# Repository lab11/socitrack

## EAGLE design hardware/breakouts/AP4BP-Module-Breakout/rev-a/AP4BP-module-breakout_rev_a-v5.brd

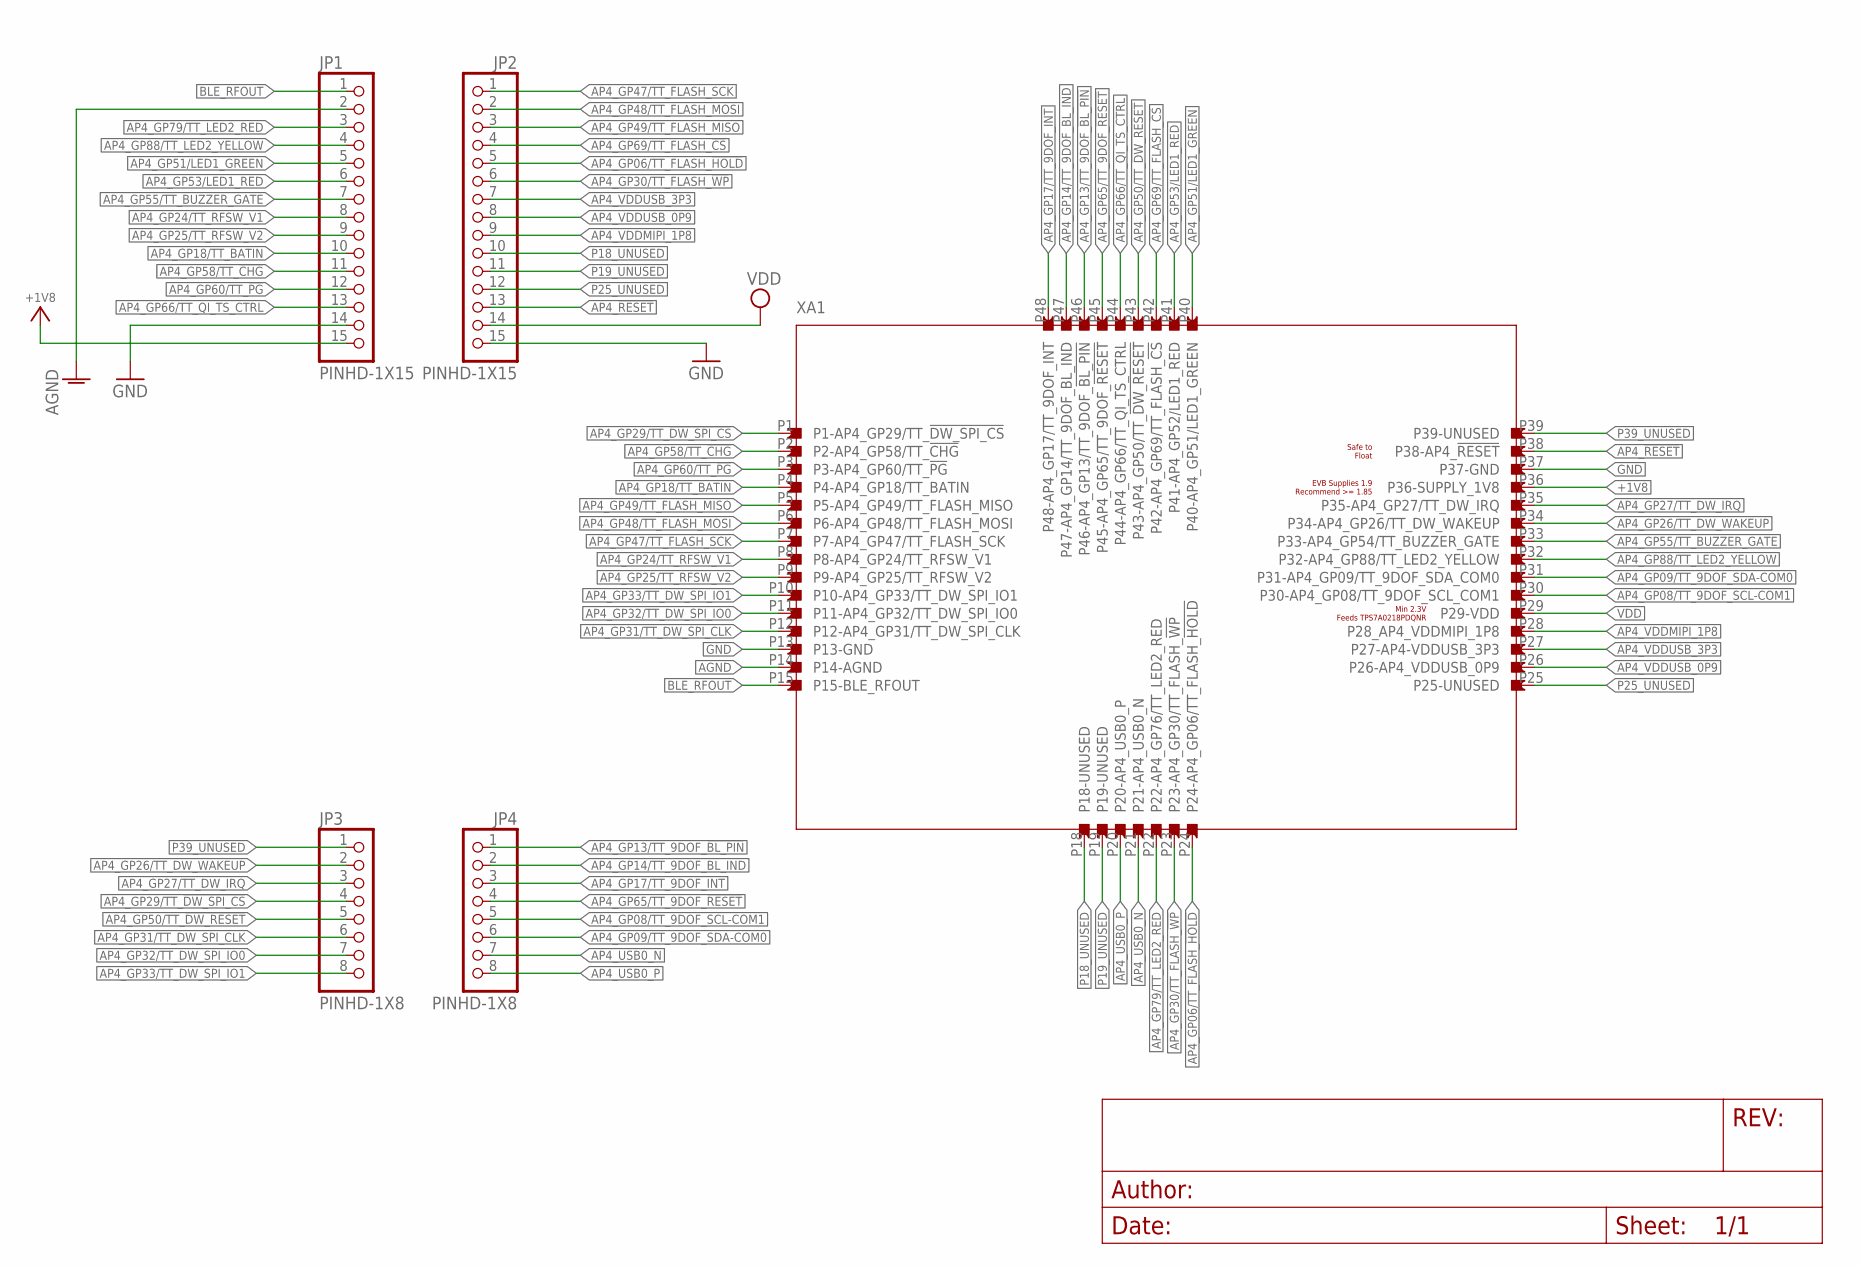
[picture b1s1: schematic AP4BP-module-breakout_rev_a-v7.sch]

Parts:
JP1, JP2: PINHD-1X15; 1X15
JP3, JP4: PINHD-1X8; 1X08
XA1: APOLLO4_BLUEPLUS_MODULE

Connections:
+1V8: JP1.15, XA1.P36 (P36-SUPPLY_1V8)
AGND: JP1.2, XA1.P14 (P14-AGND)
AP4_!RESET: JP2.13, XA1.P38 (P38-AP4_!RESET)
AP4_GP06/TT_FLASH_!HOLD: JP2.5, XA1.P24 (P24-AP4_GP06/TT_FLASH_!HOLD)
AP4_GP08/TT_9DOF_SCL-COM1: JP4.5, XA1.P30 (P30-AP4_GP08/TT_9DOF_SCL_COM1)
AP4_GP09/TT_9DOF_SDA-COM0: JP4.6, XA1.P31 (P31-AP4_GP09/TT_9DOF_SDA_COM0)
AP4_GP13/TT_9DOF_!BL_PIN: JP4.1, XA1.P46 (P46-AP4_GP13/TT_9DOF_!BL_PIN)
AP4_GP14/TT_9DOF_BL_IND: JP4.2, XA1.P47 (P47-AP4_GP14/TT_9DOF_BL_IND)
AP4_GP17/TT_9DOF_INT: JP4.3, XA1.P48 (P48-AP4_GP17/TT_9DOF_INT)
AP4_GP18/TT_BATIN: JP1.10, XA1.P4 (P4-AP4_GP18/TT_BATIN)
AP4_GP24/TT_RFSW_V1: JP1.8, XA1.P8 (P8-AP4_GP24/TT_RFSW_V1)
AP4_GP25/TT_RFSW_V2: JP1.9, XA1.P9 (P9-AP4_GP25/TT_RFSW_V2)
AP4_GP26/TT_DW_WAKEUP: JP3.2, XA1.P34 (P34-AP4_GP26/TT_DW_WAKEUP)
AP4_GP27/TT_DW_IRQ: JP3.3, XA1.P35 (P35-AP4_GP27/TT_DW_IRQ)
AP4_GP29/TT_!DW_SPI_CS: JP3.4, XA1.P1 (P1-AP4_GP29/TT_!DW_SPI_CS)
AP4_GP30/TT_FLASH_!WP: JP2.6, XA1.P23 (P23-AP4_GP30/TT_FLASH_!WP)
AP4_GP31/TT_DW_SPI_CLK: JP3.6, XA1.P12 (P12-AP4_GP31/TT_DW_SPI_CLK)
AP4_GP32/TT_DW_SPI_IO0: JP3.7, XA1.P11 (P11-AP4_GP32/TT_DW_SPI_IO0)
AP4_GP33/TT_DW_SPI_IO1: JP3.8, XA1.P10 (P10-AP4_GP33/TT_DW_SPI_IO1)
AP4_GP47/TT_FLASH_SCK: JP2.1, XA1.P7 (P7-AP4_GP47/TT_FLASH_SCK)
AP4_GP48/TT_FLASH_MOSI: JP2.2, XA1.P6 (P6-AP4_GP48/TT_FLASH_MOSI)
AP4_GP49/TT_FLASH_MISO: JP2.3, XA1.P5 (P5-AP4_GP49/TT_FLASH_MISO)
AP4_GP50/TT_!DW_RESET: JP3.5, XA1.P43 (P43-AP4_GP50/TT_!DW_RESET)
AP4_GP51/LED1_GREEN: JP1.5, XA1.P40 (P40-AP4_GP51/LED1_GREEN)
AP4_GP53/LED1_RED: JP1.6, XA1.P41 (P41-AP4_GP52/LED1_RED)
AP4_GP55/TT_BUZZER_GATE: JP1.7, XA1.P33 (P33-AP4_GP54/TT_BUZZER_GATE)
AP4_GP58/TT_!CHG: JP1.11, XA1.P2 (P2-AP4_GP58/TT_!CHG)
AP4_GP60/TT_!PG: JP1.12, XA1.P3 (P3-AP4_GP60/TT_!PG)
AP4_GP65/TT_9DOF_!RESET: JP4.4, XA1.P45 (P45-AP4_GP65/TT_9DOF_!RESET)
AP4_GP66/TT_QI_TS_CTRL: JP1.13, XA1.P44 (P44-AP4_GP66/TT_QI_TS_CTRL)
AP4_GP69/TT_FLASH_!CS: JP2.4, XA1.P42 (P42-AP4_GP69/TT_FLASH_!CS)
AP4_GP79/TT_LED2_RED: JP1.3, XA1.P22 (P22-AP4_GP76/TT_LED2_RED)
AP4_GP88/TT_LED2_YELLOW: JP1.4, XA1.P32 (P32-AP4_GP88/TT_LED2_YELLOW)
AP4_USB0_N: JP4.7, XA1.P21 (P21-AP4_USB0_N)
AP4_USB0_P: JP4.8, XA1.P20 (P20-AP4_USB0_P)
AP4_VDDMIPI_1P8: JP2.9, XA1.P28 (P28_AP4_VDDMIPI_1P8)
AP4_VDDUSB_0P9: JP2.8, XA1.P26 (P26-AP4_VDDUSB_0P9)
AP4_VDDUSB_3P3: JP2.7, XA1.P27 (P27-AP4-VDDUSB_3P3)
BLE_RFOUT: JP1.1, XA1.P15 (P15-BLE_RFOUT)
GND: JP1.14, JP2.15, XA1.P13 (P13-GND), XA1.P37 (P37-GND)
P18_UNUSED: JP2.10, XA1.P18 (P18-UNUSED)
P19_UNUSED: JP2.11, XA1.P19 (P19-UNUSED)
P25_UNUSED: JP2.12, XA1.P25 (P25-UNUSED)
P39_UNUSED: JP3.1, XA1.P39 (P39-UNUSED)
VDD: JP2.14, XA1.P29 (P29-VDD)

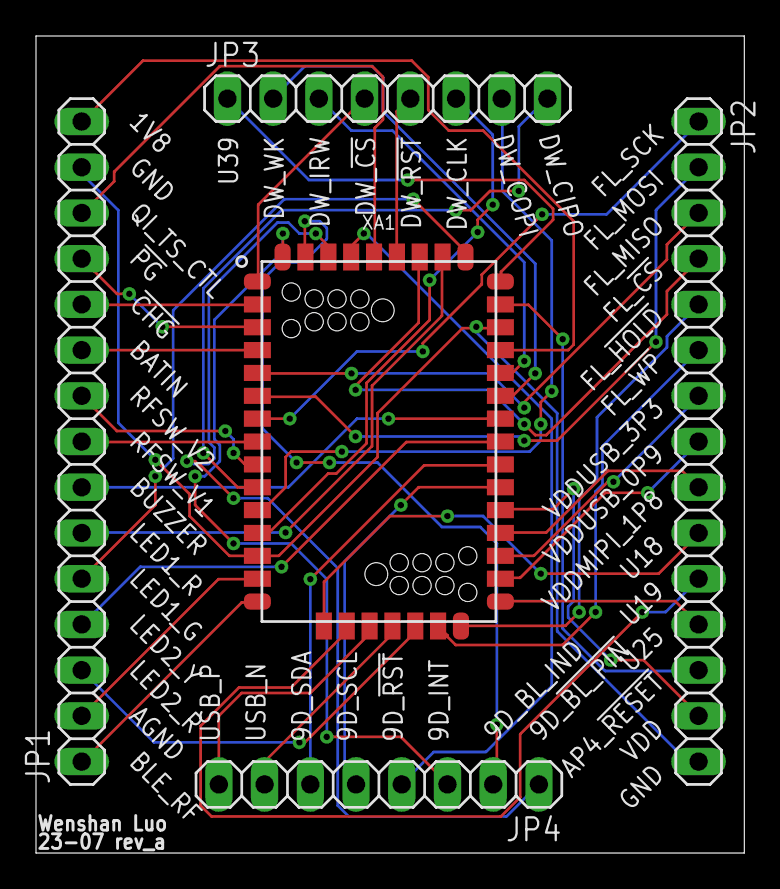
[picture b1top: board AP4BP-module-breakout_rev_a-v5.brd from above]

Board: 2 copper layers, 39.4 x 45.4 mm, 5 parts (0 on the bottom side), 45 nets.

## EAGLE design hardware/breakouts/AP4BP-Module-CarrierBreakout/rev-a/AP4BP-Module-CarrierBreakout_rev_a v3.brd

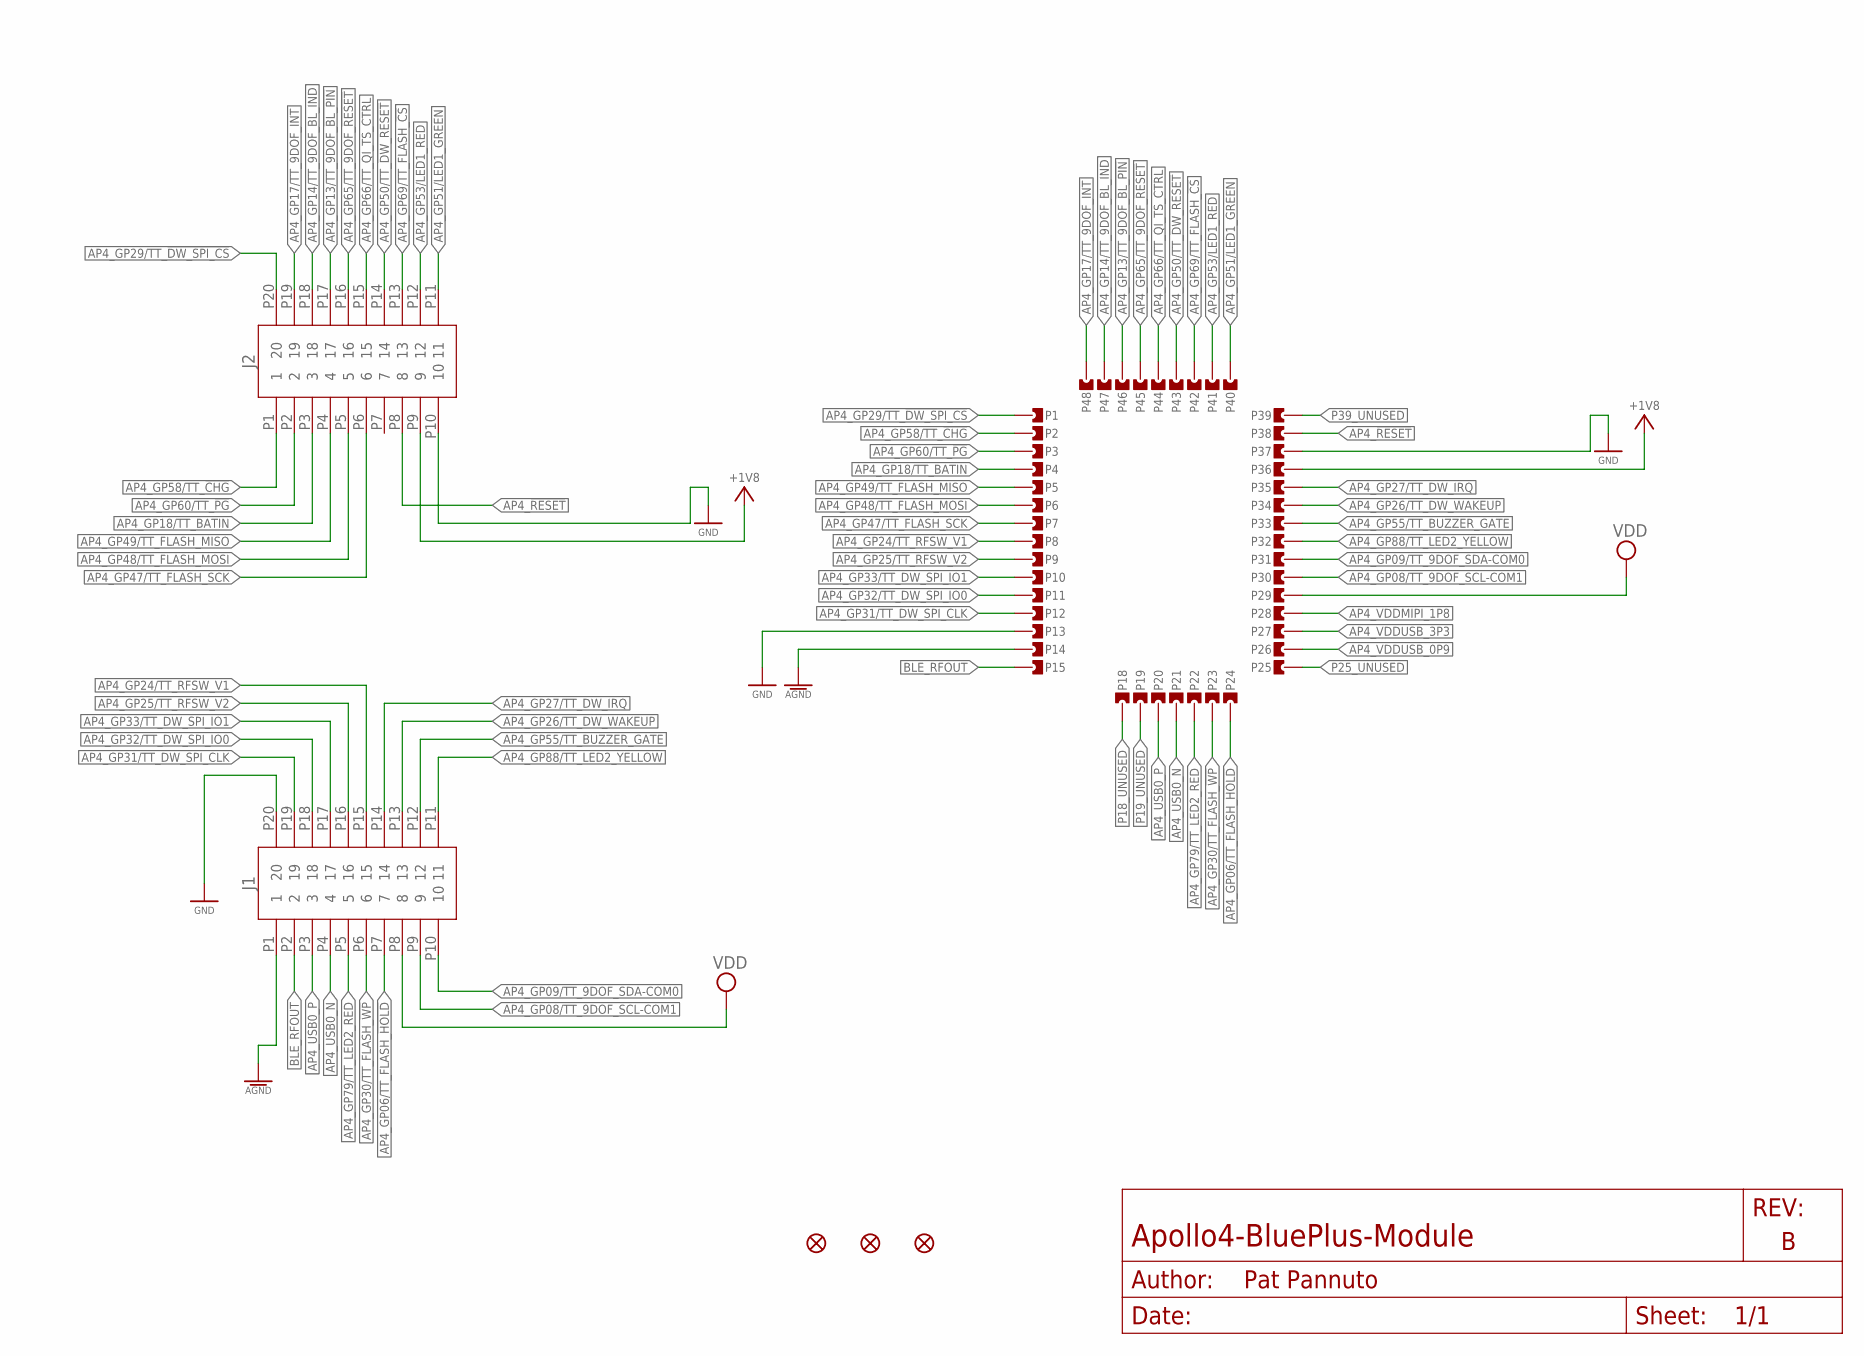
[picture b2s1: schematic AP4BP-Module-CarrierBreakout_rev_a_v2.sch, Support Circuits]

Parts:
FD1, FD2, FD3: FIDUCIALUFIDUCIAL; FIDUCIAL-MICRO
J1, J2: PINHEAD-SMD-1MM-2X10
P1, P2, P3, P4, P5, P6, P7, P8, P9, P10, P11, P12, P13, P14, P15, P18, P19, P20, P21, P22, P23, P24, P25, P26, P27, P28, P29, P30, P31, P32, P33, P34, P35, P36, P37, P38, P39, P40, P41, P42, P43, P44, P45, P46, P47, P48: CASTELLATION4L; CASTELLATION-0.55MM_DRILL-4L

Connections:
+1V8: J2.P9 (9), P36.P$1, P36.P$2, P36.P$3
AGND: J1.P1 (1), P14.P$1, P14.P$2, P14.P$3
AP4_!RESET: J2.P8 (8), P38.P$1, P38.P$2, P38.P$3
AP4_GP06/TT_FLASH_!HOLD: J1.P7 (7), P24.P$1, P24.P$2, P24.P$3
AP4_GP08/TT_9DOF_SCL-COM1: J1.P9 (9), P30.P$1, P30.P$2, P30.P$3
AP4_GP09/TT_9DOF_SDA-COM0: J1.P10 (10), P31.P$1, P31.P$2, P31.P$3
AP4_GP13/TT_9DOF_!BL_PIN: J2.P17 (17), P46.P$1, P46.P$2, P46.P$3
AP4_GP14/TT_9DOF_BL_IND: J2.P18 (18), P47.P$1, P47.P$2, P47.P$3
AP4_GP17/TT_9DOF_INT: J2.P19 (19), P48.P$1, P48.P$2, P48.P$3
AP4_GP18/TT_BATIN: J2.P3 (3), P4.P$1, P4.P$2, P4.P$3
AP4_GP24/TT_RFSW_V1: J1.P15 (15), P8.P$1, P8.P$2, P8.P$3
AP4_GP25/TT_RFSW_V2: J1.P16 (16), P9.P$1, P9.P$2, P9.P$3
AP4_GP26/TT_DW_WAKEUP: J1.P13 (13), P34.P$1, P34.P$2, P34.P$3
AP4_GP27/TT_DW_IRQ: J1.P14 (14), P35.P$1, P35.P$2, P35.P$3
AP4_GP29/TT_!DW_SPI_CS: J2.P20 (20), P1.P$1, P1.P$2, P1.P$3
AP4_GP30/TT_FLASH_!WP: J1.P6 (6), P23.P$1, P23.P$2, P23.P$3
AP4_GP31/TT_DW_SPI_CLK: J1.P19 (19), P12.P$1, P12.P$2, P12.P$3
AP4_GP32/TT_DW_SPI_IO0: J1.P18 (18), P11.P$1, P11.P$2, P11.P$3
AP4_GP33/TT_DW_SPI_IO1: J1.P17 (17), P10.P$1, P10.P$2, P10.P$3
AP4_GP47/TT_FLASH_SCK: J2.P6 (6), P7.P$1, P7.P$2, P7.P$3
AP4_GP48/TT_FLASH_MOSI: J2.P5 (5), P6.P$1, P6.P$2, P6.P$3
AP4_GP49/TT_FLASH_MISO: J2.P4 (4), P5.P$1, P5.P$2, P5.P$3
AP4_GP50/TT_!DW_RESET: J2.P14 (14), P43.P$1, P43.P$2, P43.P$3
AP4_GP51/LED1_GREEN: J2.P11 (11), P40.P$1, P40.P$2, P40.P$3
AP4_GP53/LED1_RED: J2.P12 (12), P41.P$1, P41.P$2, P41.P$3
AP4_GP55/TT_BUZZER_GATE: J1.P12 (12), P33.P$1, P33.P$2, P33.P$3
AP4_GP58/TT_!CHG: J2.P1 (1), P2.P$1, P2.P$2, P2.P$3
AP4_GP60/TT_!PG: J2.P2 (2), P3.P$1, P3.P$2, P3.P$3
AP4_GP65/TT_9DOF_!RESET: J2.P16 (16), P45.P$1, P45.P$2, P45.P$3
AP4_GP66/TT_QI_TS_CTRL: J2.P15 (15), P44.P$1, P44.P$2, P44.P$3
AP4_GP69/TT_FLASH_!CS: J2.P13 (13), P42.P$1, P42.P$2, P42.P$3
AP4_GP79/TT_LED2_RED: J1.P5 (5), P22.P$1, P22.P$2, P22.P$3
AP4_GP88/TT_LED2_YELLOW: J1.P11 (11), P32.P$1, P32.P$2, P32.P$3
AP4_USB0_N: J1.P4 (4), P21.P$1, P21.P$2, P21.P$3
AP4_USB0_P: J1.P3 (3), P20.P$1, P20.P$2, P20.P$3
AP4_VDDMIPI_1P8: P28.P$1, P28.P$2, P28.P$3
AP4_VDDUSB_0P9: P26.P$1, P26.P$2, P26.P$3
AP4_VDDUSB_3P3: P27.P$1, P27.P$2, P27.P$3
BLE_RFOUT: J1.P2 (2), P15.P$1, P15.P$2, P15.P$3
GND: J1.P20 (20), J2.P10 (10), P13.P$1, P13.P$2, P13.P$3, P37.P$1, P37.P$2, P37.P$3
P18_UNUSED: P18.P$1, P18.P$2, P18.P$3
P19_UNUSED: P19.P$1, P19.P$2, P19.P$3
P25_UNUSED: P25.P$1, P25.P$2, P25.P$3
P39_UNUSED: P39.P$1, P39.P$2, P39.P$3
VDD: J1.P8 (8), P29.P$1, P29.P$2, P29.P$3

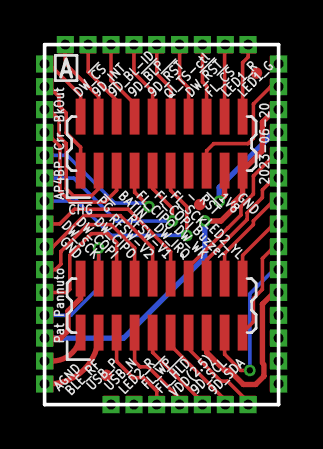
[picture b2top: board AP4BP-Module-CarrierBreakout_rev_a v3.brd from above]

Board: 2 copper layers, 13.0 x 20.0 mm, 51 parts (0 on the bottom side), 45 nets.

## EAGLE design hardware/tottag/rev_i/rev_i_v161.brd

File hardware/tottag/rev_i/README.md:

Rev i
=====

This is now stored in the Fusion Cloud (sigh), with their "version control"
(double sigh).

This is a one-off export of the state of the project when shipped to
manufacture, as well as the design files from CircuitHub (CM making boards).

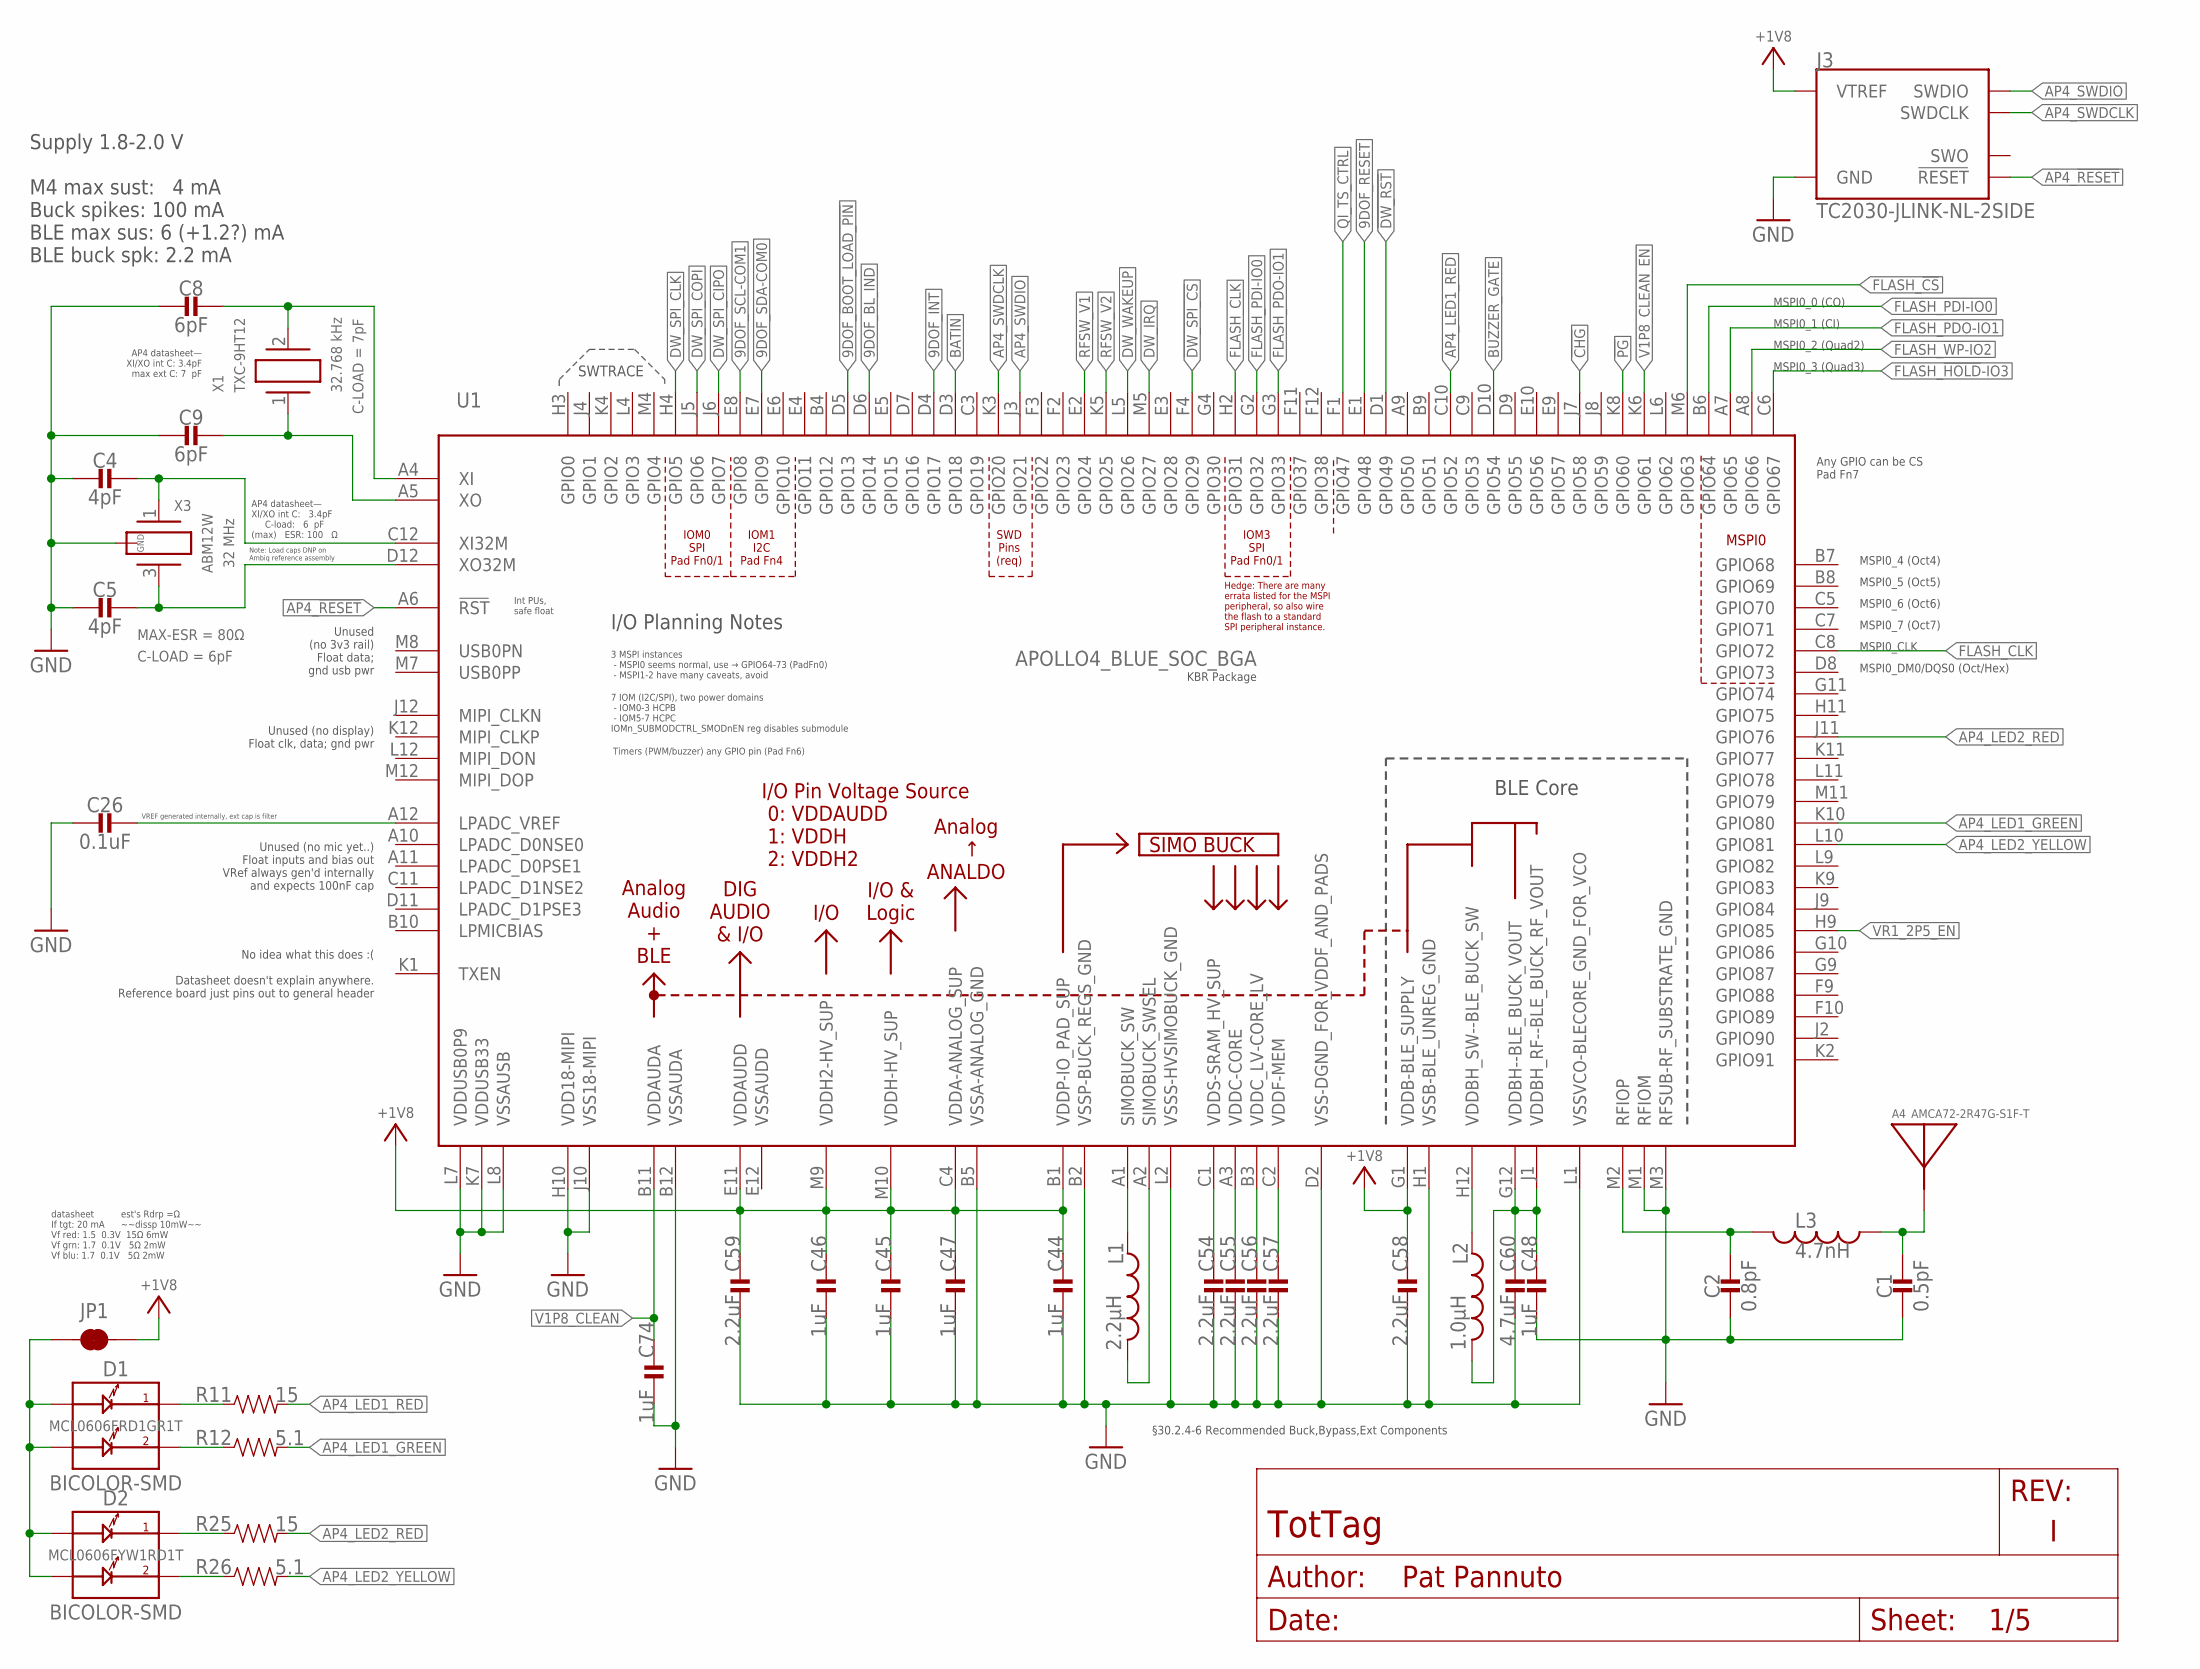
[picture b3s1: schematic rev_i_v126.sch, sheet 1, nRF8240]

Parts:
A4: AMCA72-2R47G-S1F-T; AMCA72-2R470G-S1F-T
C1: 0.5pF; 0402_CAP; MPN GJM1555C1HR50WB01D
C2: 0.8pF; 0402_CAP; MPN GJM1555C1HR80WB01D
C4, C5: 4pF; 0201_CAP; MPN GRM0335C1H4R0BA01D
C8, C9: 6pF; 0201_CAP; MPN GRM0335C1H6R0BA01D
C26: 0.1uF; 0201_CAP; MPN CL05A104KP5NNNC
C44, C45, C46, C47, C48, C74: 1uF; 0201_CAP; MPN GRM033R61A105ME44D
C54, C55, C56, C57, C58, C59: 2.2uF; 0201_CAP; MPN GRM033R61A225KE47D
C60: 4.7uF; 0402_CAP; MPN CL05A475MP5NRNC
D1: BICOLOR-SMD; LED-0606; MPN MCL0606FRD1GR1T
D2: BICOLOR-SMD; LED-0606; MPN MCL0606FYW1RD1T
J3: TC2030-JLINK-NL-2SIDE; TC2030-IDC-NL-2SIDE
JP1: JUMPER-SMT_2_NC_TRACE_SILK; SMT-JUMPER_2_NC_TRACE_SILK
L1: 2.2µH; 0805_CAP; MPN DFE201210U-2R2M=P2
L2: 1.0µH; 0603_CAP; MPN DFE18SAN1R0ME0L
L3: 4.7nH; 0402_CAP; MPN LQW15AN4N7G8ZD
R11, R25: 15; 0402_RES; MPN RC0402JR-0715RL
R12, R26: 5.1; 0402_RES; MPN RC0402JR-075R1L
U1: APOLLO4_BLUE_SOC_BGA
X1: TXC-9HT12; MPN 9HT12-32.768KDZY-T
X3: ABM12W; MPN ABM12W-32.0000MHZ-6-D1X-T3

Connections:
9DOF_!BOOT_LOAD_PIN: U1.D5 (GPIO13); also elsewhere on the board
9DOF_!RESET: U1.E1 (GPIO48); also elsewhere on the board
9DOF_BL_IND: U1.D6 (GPIO14); also elsewhere on the board
9DOF_INT: U1.D4 (GPIO17); also elsewhere on the board
9DOF_SCL-COM1: U1.E8 (GPIO8); also elsewhere on the board
9DOF_SDA-COM0: U1.E7 (GPIO9); also elsewhere on the board
!CHG: U1.J7 (GPIO58); also elsewhere on the board
!DW_RST: U1.D1 (GPIO49); also elsewhere on the board
!DW_SPI_CS: U1.F4 (GPIO29); also elsewhere on the board
!PG: U1.K8 (GPIO60); also elsewhere on the board
+1V8: C44.P$1 (1), C45.P$1 (1), C46.P$1 (1), C47.P$1 (1), C58.P$1 (1), C59.P$1 (1), J3.1 (VTREF), J3.B1 (VTREF), JP1.2, U1.B1 (VDDP-IO_PAD_SUP), U1.C4 (VDDA-ANALOG_SUP), U1.E11 (VDDAUDD), U1.G1 (VDDB-BLE_SUPPLY), U1.M9 (VDDH2-HV_SUP), U1.M10 (VDDH-HV_SUP); also elsewhere on the board
AP4_!RESET: J3.3 (!RESET), J3.B3 (!RESET), U1.A6 (!RST)
AP4_LED1_GREEN: R12.2, U1.K10 (GPIO80); also elsewhere on the board
AP4_LED1_RED: R11.2, U1.C10 (GPIO52); also elsewhere on the board
AP4_LED2_BLUE_COMM: D1.1-C1 (C1), R11.1
AP4_LED2_RED: R25.2, U1.J11 (GPIO76); also elsewhere on the board
AP4_LED2_YELLOW: R26.2, U1.L10 (GPIO81); also elsewhere on the board
AP4_LED_BLUE_COMM: D2.2-C2 (C2), R26.1
AP4_LED_GREEN_COMM: D2.1-C1 (C1), R25.1
AP4_LED_RED_COMM: D1.2-C2 (C2), R12.1
AP4_LPADC_VREF: C26.P$1 (1), U1.A12 (LPADC_VREF)
AP4_RFIOP: C2.1, L3.2, U1.M2 (RFIOP)
AP4_SWDCLK: J3.4 (SWDCLK), J3.B4 (SWDCLK), U1.K3 (GPIO20)
AP4_SWDIO: J3.2 (SWDIO), J3.B2 (SWDIO), U1.J3 (GPIO21)
AP4_VDDBH: C48.P$1 (1), C60.1, L2.2, U1.G12 (VDDBH--BLE_BUCK_VOUT), U1.J1 (VDDBH_RF--BLE_BUCK_RF_VOUT)
AP4_VDDBH_SW: L2.1, U1.H12 (VDDBH_SW--BLE_BUCK_SW)
AP4_VDDC: C55.P$1 (1), U1.A3 (VDDC-CORE)
AP4_VDDC_LV: C56.P$1 (1), U1.B3 (VDDC_LV-CORE_LV)
AP4_VDDF: C57.P$1 (1), U1.C2 (VDDF-MEM)
AP4_VDDS: C54.P$1 (1), U1.C1 (VDDS-SRAM_HV_SUP)
AP4_XI: C8.P$1 (1), U1.A4 (XI), X1.2
AP4_XI32M: C4.P$1 (1), U1.C12 (XI32M), X3.1
AP4_XO: C9.P$1 (1), U1.A5 (XO), X1.1
AP4_XO32M: C5.P$1 (1), U1.D12 (XO32M), X3.3 (2)
BATIN: U1.D3 (GPIO18); also elsewhere on the board
BLE_ANT_FEED: A4.S1, C1.1, L3.1
BUZZER_GATE: U1.D10 (GPIO54); also elsewhere on the board
DW_IRQ: U1.M5 (GPIO27); also elsewhere on the board
DW_SPI_CIPO: U1.J6 (GPIO7); also elsewhere on the board
DW_SPI_CLK: U1.H4 (GPIO5); also elsewhere on the board
DW_SPI_COPI: U1.J5 (GPIO6); also elsewhere on the board
DW_WAKEUP: U1.L5 (GPIO26); also elsewhere on the board
FLASH_!CS: U1.M6 (GPIO63); also elsewhere on the board
FLASH_!HOLD!-IO3: U1.C6 (GPIO67); also elsewhere on the board
FLASH_!WP!-IO2: U1.A8 (GPIO66); also elsewhere on the board
FLASH_CLK: U1.C8 (GPIO72), U1.H2 (GPIO31); also elsewhere on the board
FLASH_PDI-IO0: U1.B6 (GPIO64), U1.G2 (GPIO32); also elsewhere on the board
FLASH_PDO-IO1: U1.A7 (GPIO65), U1.G3 (GPIO33); also elsewhere on the board
GND: C1.2, C2.2, C4.P$2 (2), C5.P$2 (2), C8.P$2 (2), C9.P$2 (2), C26.P$2 (2), C44.P$2 (2), C45.P$2 (2), C46.P$2 (2), C47.P$2 (2), C48.P$2 (2), C54.P$2 (2), C55.P$2 (2), C56.P$2 (2), C57.P$2 (2), C58.P$2 (2), C59.P$2 (2), C60.2, C74.P$2 (2), J3.5 (GND), J3.B5 (GND), U1.B2 (VSSP-BUCK_REGS_GND), U1.B5 (VSSA-ANALOG_GND), U1.B12 (VSSAUDA), U1.D2 (VSS-DGND_FOR_VDDF_AND_PADS), U1.H1 (VSSB-BLE_UNREG_GND), U1.H10 (VDD18-MIPI), U1.J10 (VSS18-MIPI), U1.K7 (VDDUSB33), U1.L1 (VSSVCO-BLECORE_GND_FOR_VCO), U1.L2 (VSSS-HVSIMOBUCK_GND), U1.L7 (VDDUSB0P9), U1.L8 (VSSAUSB), U1.M1 (RFIOM), U1.M3 (RFSUB-RF_SUBSTRATE_GND), X3.2 (GND), X3.4 (GND); also elsewhere on the board
LED_SUP: D1.3-A1 (A1), D1.4-A2 (A2), D2.3-A1 (A1), D2.4-A2 (A2), JP1.1
unnamed: L1.P$1 (1), U1.A1 (SIMOBUCK_SW)
unnamed: L1.P$2 (2), U1.A2 (SIMOBUCK_SWSEL)
QI_TS_CTRL: U1.F1 (GPIO47); also elsewhere on the board
RFSW_V1: U1.E2 (GPIO24); also elsewhere on the board
RFSW_V2: U1.K5 (GPIO25); also elsewhere on the board
V1P8_CLEAN: C74.P$1 (1), U1.B11 (VDDAUDA); also elsewhere on the board
V1P8_CLEAN_EN: U1.K6 (GPIO61); also elsewhere on the board
VR1_2P5_EN: U1.H9 (GPIO85); also elsewhere on the board

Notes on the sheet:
Supply 1.8-2.0 V M4 max sust: 4 mA Buck spikes: 100 mA BLE max sus: 6 (+1.2?) mA BLE buck spk: 2.2 mA
Note: Load caps DNP on Ambiq reference assembly
Int PUs, safe float
Unused (no 3v3 rail) Float data; gnd usb pwr
Unused (no display) Float clk, data; gnd pwr
Unused (no mic yet..) Float inputs and bias out VRef always gen'd internally and expects 100nF cap
No idea what this does :( Datasheet doesn't explain anywhere. Reference board just pins out to general header
I/O Planning Notes
3 MSPI instances - MSPI0 seems normal, use → GPIO64-73 (PadFn0) - MSPI1-2 have many caveats, avoid
7 IOM (I2C/SPI), two power domains - IOM0-3 HCPB - IOM5-7 HCPC IOMn_SUBMODCTRL_SMODnEN reg disables submodule
MSPI0
IOM0 SPI Pad Fn0/1
IOM1 I2C Pad Fn4
Timers (PWM/buzzer) any GPIO pin (Pad Fn6)
MSPI0_1 (CI)
MSPI0_0 (CO)
MSPI0_7 (Oct7)
MSPI0_6 (Oct6)
MSPI0_5 (Oct5)
MSPI0_4 (Oct4)
MSPI0_3 (Quad3)
MSPI0_2 (Quad2)
MSPI0_CLK
MSPI0_DM0/DQS0 (Oct/Hex)
KBR Package
Any GPIO can be CS Pad Fn7
datasheet est's Rdrp =Ω If tgt: 20 mA ~~dissp 10mW~~ Vf red: 1.5 0.3V 15Ω 6mW Vf grn: 1.7 0.1V 5Ω 2mW Vf blu: 1.7 0.1V 5Ω 2mW
§30.2.4-6 Recommended Buck,Bypass,Ext Components
SWTRACE
SWD Pins (req)
VREF generated internally, ext cap is filter
IOM3 SPI Pad Fn0/1
Hedge: There are many errata listed for the MSPI peripheral, so also wire the flash to a standard SPI peripheral instance.
AP4 datasheet— XI/XO int C: 3.4pF max ext C: 7 pF
AP4 datasheet— XI/XO int C: 3.4pF C-load: 6 pF (max) ESR: 100 Ω

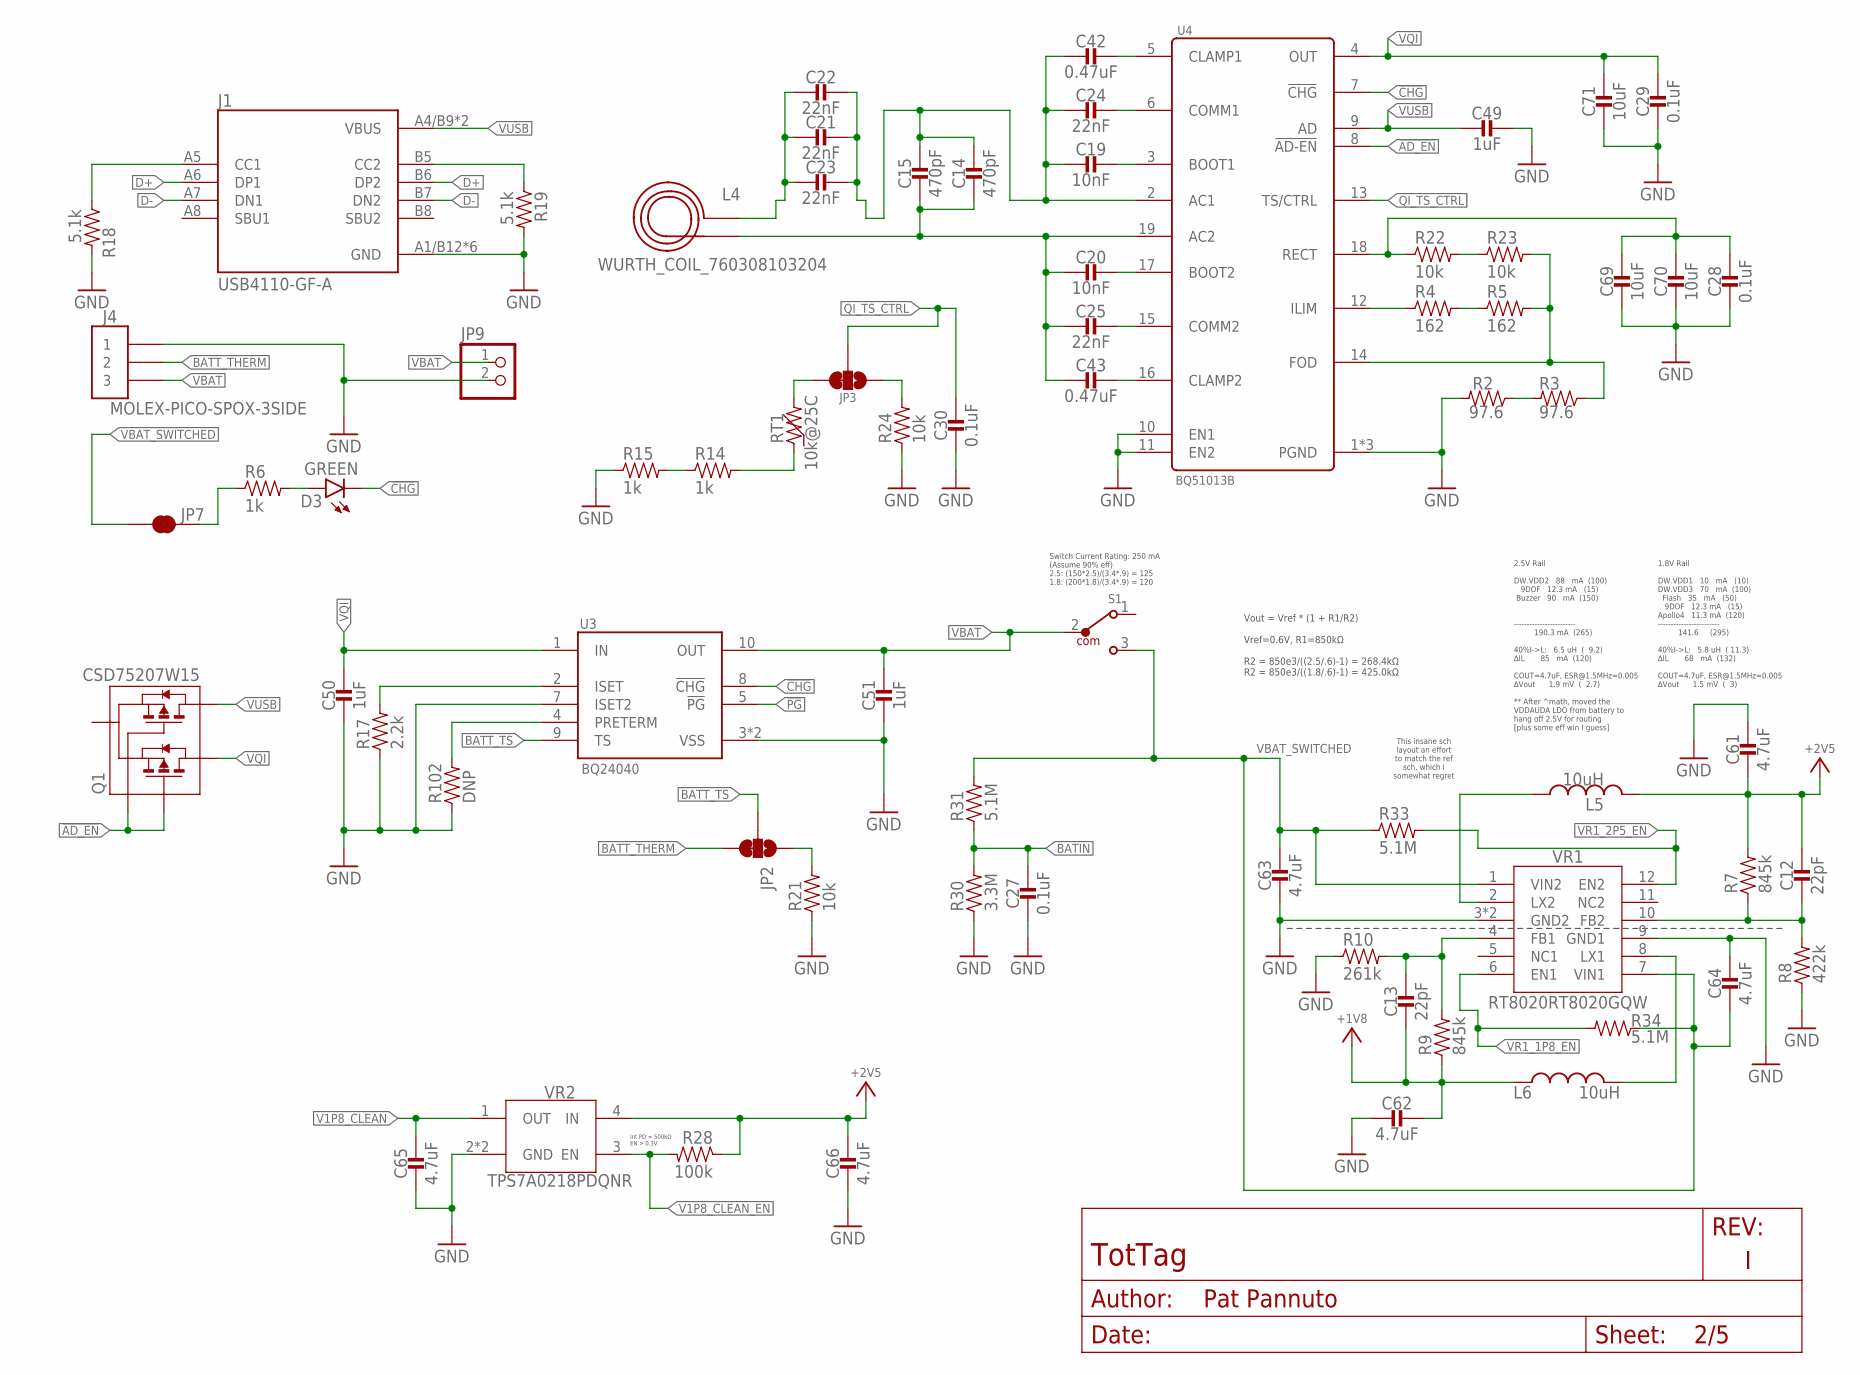
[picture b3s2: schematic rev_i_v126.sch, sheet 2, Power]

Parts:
C12, C13: 22pF; 0201_CAP; MPN GRM0335C1H220FA01D
C14, C15: 470pF; 0402_CAP; MPN GRM1555C1H471JA01J; DIGIKEY 490-6242-1-ND
C19, C20: 10nF; 0402_CAP; MPN GRM155R71H103KA88J; DIGIKEY 490-6351-2-ND
C21, C22, C23: 22nF; 0402_CAP; MPN GRM155R71E223JA61D; DIGIKEY 490-10699-2-ND
C24, C25: 22nF; 0402_CAP; MPN CC0402ZRY5V8BB223; DIGIKEY 311-3823-1-ND
C27, C28, C29, C30: 0.1uF; 0402_CAP; MPN GRM155R71C104KA88J; DIGIKEY 490-6328-1-ND
C42, C43: 0.47uF; 0402_CAP; MPN GRT155R61E474ME01D; DIGIKEY 490-12270-1-ND
C49, C50, C51: 1uF; 0402_CAP; MPN GRM155R70G105KA12D; DIGIKEY 490-7195-1-ND
C61, C62, C63, C64, C65, C66: 4.7uF; 0805_CAP; MPN JMK212ABJ475MGHT
C69, C70, C71: 10uF; 0603_CAP; MPN CM105X5R106M25AT; DIGIKEY 1253-CM105X5R106M25ATCT-ND
D3: GREEN; LED-0603; MPN LTST-C191KGKT; DIGIKEY 160-1446-1-ND
J1: USB4110-GF-A; GCT_USB4110-GF-A
J4: MOLEX-PICO-SPOX-3SIDE; MOLEX-PICO-SPOX-3_SIDE
JP2, JP3: JUMPER-SMT_3_1-NC_TRACE_SILK; SMT-JUMPER_3_1-NC_TRACE_SILK
JP7: JUMPER-SMT_2_NC_TRACE_SILK; SMT-JUMPER_2_NC_TRACE_SILK
JP9: PINHD-1X2; 1X02
L4: WURTH_COIL_760308103204
L5, L6: 10uH; NRX3015; MPN NR3015T100M
Q1: CSD75207W15; DSBGA
R2, R3: 97.6; 0402_RES; MPN RMCF0402FT97R6; DIGIKEY RMCF0402FT97R6CT-ND
R4, R5: 162; 0402_RES; MPN RMCF0402FT162R; DIGIKEY RMCF0402FT162RCT-ND
R6, R14, R15: 1k; 0402_RES
R7, R9: 845k; 0201_RES; MPN ERJ-1GNF8453C
R8: 422k; 0201_RES; MPN ERJ-1GNF4223C
R10: 261k; 0201_RES; MPN ERJ-1GNF2613C
R17: 2.2k; 0402_RES; MPN RMCF0402JT2K20; DIGIKEY RMCF0402JT2K20CT-ND
R18, R19: 5.1k; 0402_RES; MPN RMCF0402FT5K10; DIGIKEY RMCF0402FT5K10CT-ND
R21, R22, R23, R24: 10k; 0402_RES; MPN RC0402JR-0710KL; DIGIKEY 311-10KJRCT-ND
R28: 100k; 0402_RES; MPN RT0402BRE07100KL
R30: 3.3M; 0402_RES; MPN RMCF0402FT3M30; DIGIKEY RMCF0402FT3M30CT-ND
R31, R33, R34: 5.1M; 0402_RES; MPN RMCF0402FT5M10; DIGIKEY RMCF0402FT5M10CT-ND
R102: DNP; 0402_RES
RT1: 10k@25C; 0402_RES; MPN NCU15XH103F60RC; DIGIKEY 490-18149-1-ND
S1: 450404015514; DIGIKEY 732-13665-1-ND
U3: BQ24040; DSQ0010A
U4: BQ51013B; RHL0020A
VR1: RT8020RT8020GQW; SON45P300X300X80-13T160X250N
VR2: TPS7A0218PDQNR; 4-XDFN-EP

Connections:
!AD_EN: Q1.A1 (G1), Q1.C1 (G2), U4.8 (!AD-EN)
!CHG: D3.C, U3.8 (!CHG), U4.7 (!CHG); also elsewhere on the board
!PG: U3.5 (!PG); also elsewhere on the board
+1V8: C13.P$2 (2), C62.P$1 (1), L6.P$1 (1), R9.1; also elsewhere on the board
+2V5: C12.P$1 (1), C61.P$2 (2), C66.P$1 (1), L5.P$2 (2), R7.2, R28.1, VR2.4 (IN); also elsewhere on the board
BATIN: C27.1, R30.2, R31.1; also elsewhere on the board
BATT_THERM: J4.2, J4.2SUPP (2), JP2.3
BATT_TS: JP2.2, U3.9 (TS)
BQ_AC1: C14.1, C15.1, C19.2, C21.1, C22.1, C23.1, C24.2, C42.2, U4.2 (AC1)
BQ_AC2: C14.2, C15.2, C20.2, C25.2, C43.2, L4.P$2 (2), U4.19 (AC2)
BQ_BOOT1: C19.1, U4.3 (BOOT1)
BQ_BOOT2: C20.1, U4.17 (BOOT2)
BQ_CLAMP1: C42.1, U4.5 (CLAMP1)
BQ_CLAMP2: C43.1, U4.16 (CLAMP2)
BQ_COMM1: C24.1, U4.6 (COMM1)
BQ_COMM2: C25.1, U4.15 (COMM2)
BQ_FOD: R3.1, R5.2, R23.2, U4.14 (FOD)
BQ_ILM: R4.1, U4.12 (ILIM)
BQ_ISET: R17.2, U3.2 (ISET)
BQ_RECT: C28.1, C69.1, C70.1, R22.1, U4.18 (RECT)
COIL_AC1: C21.2, C22.2, C23.2, L4.P$1 (1)
D+: J1.A6 (DP1), J1.B6 (DP2)
D-: J1.A7 (DN1), J1.B7 (DN2)
GND: C27.2, C28.2, C29.2, C30.2, C49.1, C50.2, C51.2, C61.P$1 (1), C62.P$2 (2), C63.P$2 (2), C64.P$1 (1), C65.P$2 (2), C66.P$2 (2), C69.2, C70.2, C71.2, J1.A1/B12 (GND), J1.B1/A12 (GND), J1.S1 (GND), J1.S2 (GND), J1.S3 (GND), J1.S4 (GND), J4.1, J4.1SUPP (1), JP9.2, R2.2, R8.1, R10.1, R15.1, R17.1, R18.2, R19.2, R21.1, R24.1, R30.1, R102.1, U3.3 (VSS), U3.7 (ISET2), U3.PAD (VSS), U4.1 (PGND), U4.10 (EN1), U4.11 (EN2), U4.20 (PGND), U4.PAD (PGND), VR1.3 (GND2), VR1.9 (GND1), VR1.13 (GND2), VR2.2 (GND), VR2.PAD (GND); also elsewhere on the board
unnamed: J1.B5 (CC2), R19.1
unnamed: J1.A5 (CC1), R18.1
unnamed: R2.1, R3.2
unnamed: JP2.1, R21.2
unnamed: R102.2, U3.4 (PRETERM)
unnamed: D3.A, R6.2
unnamed: R22.2, R23.1
unnamed: R4.2, R5.1
unnamed: JP3.1, R24.2
unnamed: JP3.3, RT1.2
unnamed: R14.2, RT1.1
unnamed: R14.1, R15.2
QI_TS_CTRL: C30.1, JP3.2, U4.13 (TS/CTRL); also elsewhere on the board
V1P8_CLEAN: C65.P$1 (1), VR2.1 (OUT); also elsewhere on the board
V1P8_CLEAN_EN: R28.2, VR2.3 (EN); also elsewhere on the board
VBAT: C51.1, J4.3, J4.3SUPP (3), JP9.1, S1.2, U3.10 (OUT)
VBAT_SWITCHED: C63.P$1 (1), C64.P$2 (2), JP7.1, R31.2, R33.1, R34.1, S1.3, VR1.1 (VIN2), VR1.7 (VIN1); also elsewhere on the board
VBAT_SW_FOR_CHGLED: JP7.2, R6.1
VQI: C29.1, C50.1, C71.1, Q1.A2 (D1), Q1.A3 (D1), Q1.B3 (D1), U3.1 (IN), U4.4 (OUT)
VR1_1P8_EN: R34.2, VR1.6 (EN1)
VR1_2P5_EN: R33.2, VR1.12 (EN2); also elsewhere on the board
VR1_FB1: C13.P$1 (1), R9.2, R10.2, VR1.4 (FB1)
VR1_FB2: C12.P$2 (2), R7.1, R8.2, VR1.10 (FB2)
VR1_LX1: L6.P$2 (2), VR1.8 (LX1)
VR1_LX2: L5.P$1 (1), VR1.2 (LX2)
VUSB: C49.2, J1.A4/B9 (VBUS), J1.B4/A9 (VBUS), Q1.B2 (D2), Q1.C2 (D2), Q1.C3 (D2), U4.9 (AD)

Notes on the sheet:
2.5V Rail DW.VDD2 88 mA (100) 9DOF 12.3 mA (15) Buzzer 90 mA (150) ------------------------ 190.3 mA (265) 40%I->L: 6.5 uH ( 9.2) ∆IL 85 mA (120) COUT=4.7uF, ESR@1.5MHz=0.005 ∆Vout 1.9 mV ( 2.7) ** After ^math, moved the VDDAUDA LDO from battery to hang off 2.5V for routing [plus some eff win I gue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
1.8V Rail DW.VDD1 10 mA (10) DW.VDD3 70 mA (100) Flash 35 mA (50) 9DOF 12.3 mA (15) Apollo4 11.3 mA (120) ------------------------ 141.6 (295) 40%I->L: 5.8 uH ( 11.3) ∆IL 68 mA (132) COUT=4.7uF, ESR@1.5MHz=0.005 ∆Vout 1.5 mV ( 3)
Vout = Vref * (1 + R1/R2) Vref=0.6V, R1=850kΩ R2 = 850e3/((2.5/.6)-1) = 268.4kΩ R2 = 850e3/((1.8/.6)-1) = 425.0kΩ
This insane sch layout an effort to match the ref sch, which I somewhat regret
Int PD = 500kΩ EN > 0.3V
Switch Current Rating: 250 mA (Assume 90% eff) 2.5: (150*2.5)/(3.4*.9) = 125 1.8: (200*1.8)/(3.4*.9) = 120

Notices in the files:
parts and their libraries:
SparkFun-Aesthetics: Licensing: Creative Commons ShareAlike 4.0 International - https://creativecommons.org/licenses/by-sa/4.0
SparkFun-LED: Licensing: CC v3.0 Share-Alike You are welcome to use this library for commercial purposes.
Wurth_Switch_WS-SLSU: Copyright: Würth Elektronik
